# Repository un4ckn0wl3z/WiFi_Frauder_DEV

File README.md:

# WiFi Frauder 🚨📡

**WiFi Frauder** is an open-source hardware and firmware project designed to broadcast humorous or custom WiFi SSIDs using an ESP32-based custom PCB.

---

## 🟩 PCB Overview

---

## 🔧 Features

- Random (Slow) – Randomly spams WiFi SSIDs at a slow rate
- Random (Fast) – Randomly spams WiFi SSIDs at a faster rate
- Custom SSID – Spams WiFi SSIDs based on entries from the SPIFFS config file

---

## To stop spamming
- Press both the UP and DOWN buttons simultaneously to stop spamming.

---

## 🛠️ Hardware

- **Microcontroller**: ESP32 DevKitC 32E (38 pins)
- **Power**: USB or battery-powered
- **Display**: SSD1306 0.96 I2C OLED

PCB design files and schematics are included in the `/pcb` folder.

---

## 📦 Firmware

Written in C++ using the Arduino and FreeRTOS frameworks, built with the PlatformIO toolset.
First, build the SPIFFS file system and edit the SSIDs as you like in the `funny_ssid_list.txt` file located in the `/data` folder.
Then, build the main firmware and upload it to the `WiFi Frauder` device.

---
## Disclaimer

⚠️ Intended for educational and ethical hacking use only. Use responsibly and **never** violate local laws or network policies.

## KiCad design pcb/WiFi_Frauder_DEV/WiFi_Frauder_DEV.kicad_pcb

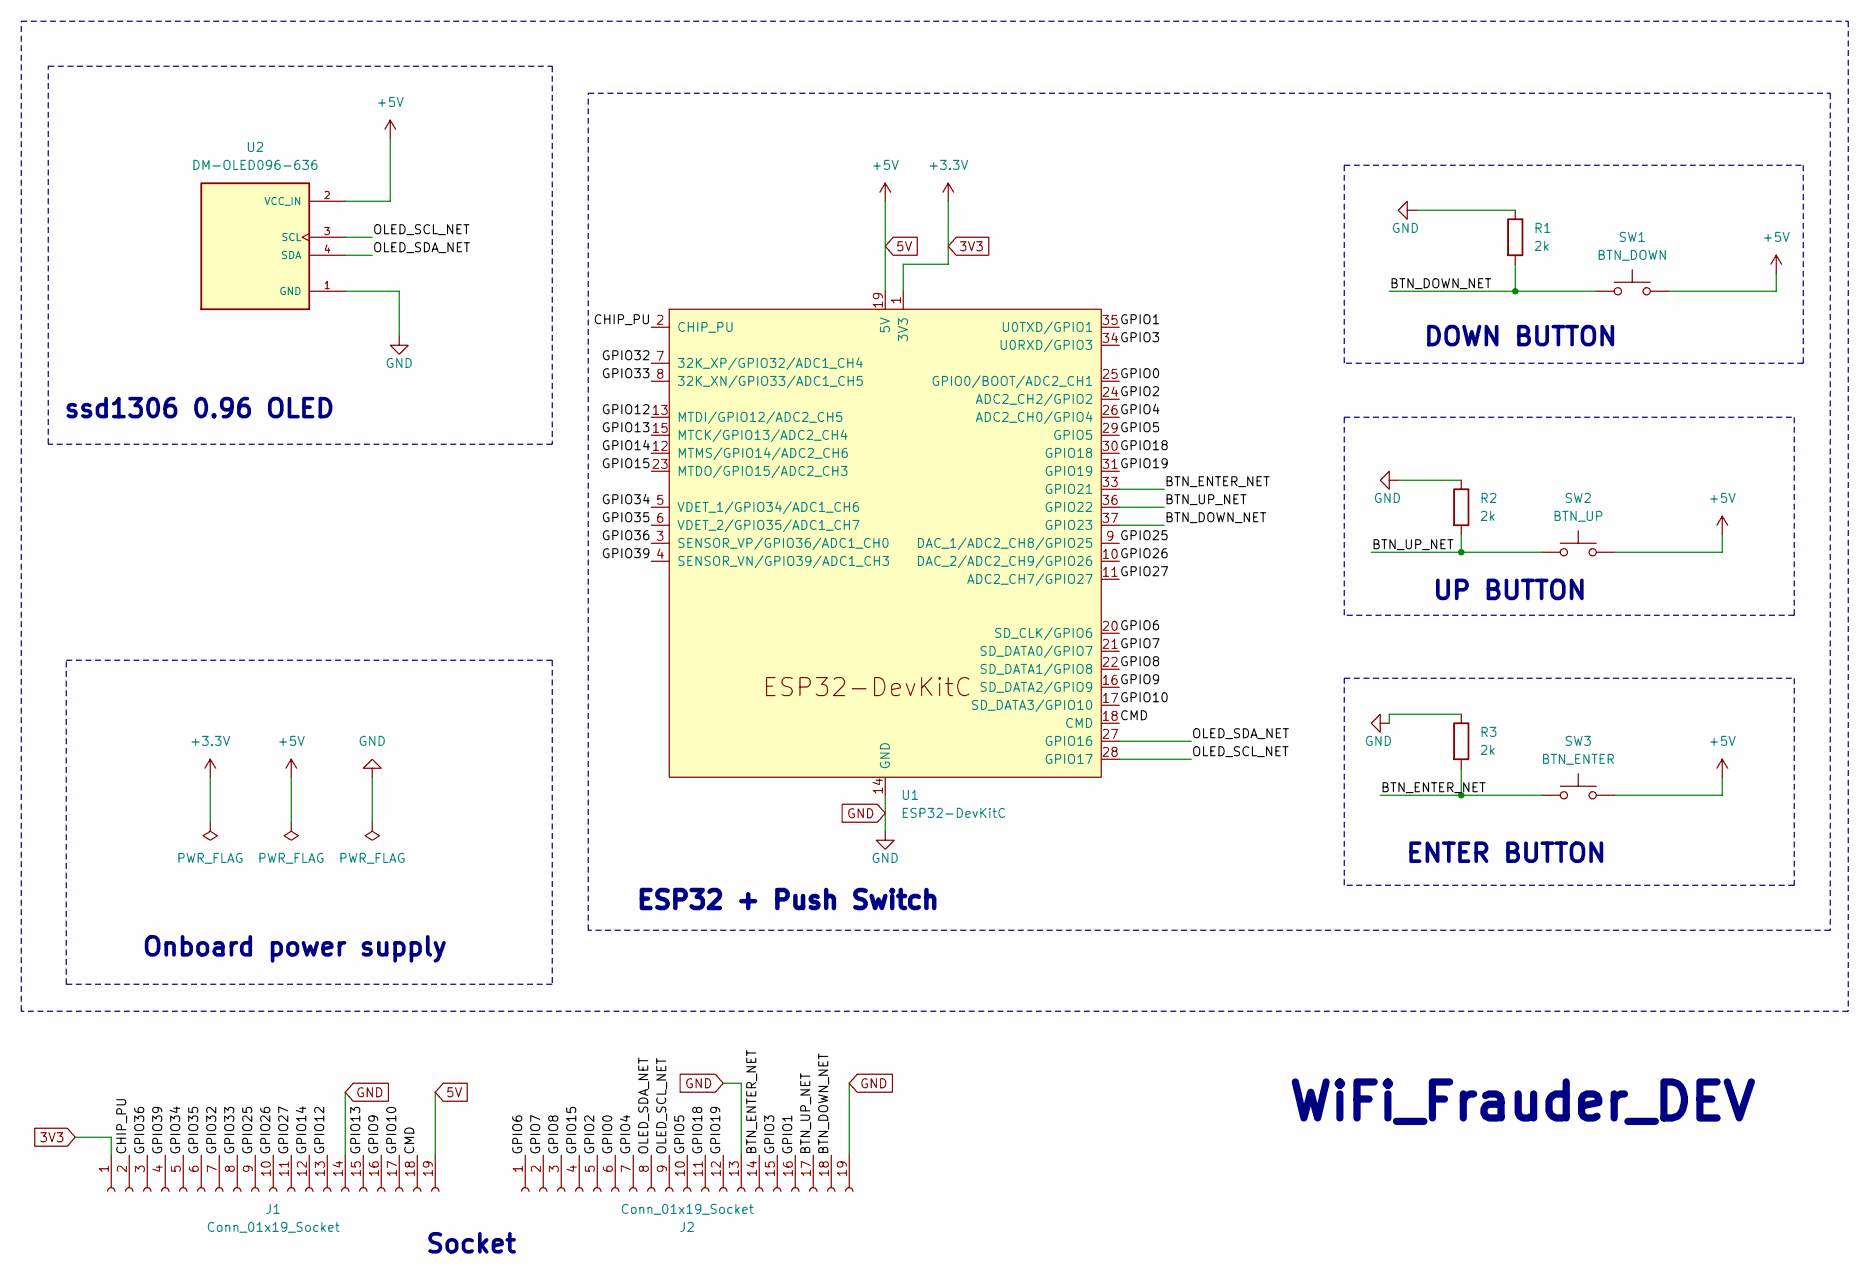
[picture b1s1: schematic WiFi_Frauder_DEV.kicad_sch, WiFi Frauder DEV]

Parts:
J1, J2: Conn_01x19_Socket; PinSocket_1x19_P2.54mm_Vertical
R1, R2, R3: 2k; R_Axial_DIN0207_L6.3mm_D2.5mm_P10.16mm_Horizontal
SW1: BTN_DOWN; SW_PUSH_6mm
SW2: BTN_UP; SW_PUSH_6mm
SW3: BTN_ENTER; SW_PUSH_6mm
U1: ESP32-DevKitC
U2: DM-OLED096-636; MODULE_DM-OLED096-636; PARTREV 2018-09-10

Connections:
3V3: J1.1, U1.1 (3V3)
5V: J1.19, SW1.2, SW2.2, SW3.2, U1.19 (5V), U2.2 (VCC_IN)
/BTN_DOWN_NET: J2.18, R1.2, SW1.1, U1.37 (GPIO23)
/BTN_ENTER_NET: J2.14, R3.2, SW3.1, U1.33 (GPIO21)
/BTN_UP_NET: J2.17, R2.2, SW2.1, U1.36 (GPIO22)
/CHIP_PU: J1.2, U1.2 (CHIP_PU)
/CMD: J1.18, U1.18 (CMD)
/GPIO0: J2.6, U1.25 (GPIO0/BOOT/ADC2_CH1)
/GPIO1: J2.16, U1.35 (U0TXD/GPIO1)
/GPIO2: J2.5, U1.24 (ADC2_CH2/GPIO2)
/GPIO3: J2.15, U1.34 (U0RXD/GPIO3)
/GPIO4: J2.7, U1.26 (ADC2_CH0/GPIO4)
/GPIO5: J2.10, U1.29 (GPIO5)
/GPIO6: J2.1, U1.20 (SD_CLK/GPIO6)
/GPIO7: J2.2, U1.21 (SD_DATA0/GPIO7)
/GPIO8: J2.3, U1.22 (SD_DATA1/GPIO8)
/GPIO9: J1.16, U1.16 (SD_DATA2/GPIO9)
/GPIO10: J1.17, U1.17 (SD_DATA3/GPIO10)
/GPIO12: J1.13, U1.13 (MTDI/GPIO12/ADC2_CH5)
/GPIO13: J1.15, U1.15 (MTCK/GPIO13/ADC2_CH4)
/GPIO14: J1.12, U1.12 (MTMS/GPIO14/ADC2_CH6)
/GPIO15: J2.4, U1.23 (MTDO/GPIO15/ADC2_CH3)
/GPIO18: J2.11, U1.30 (GPIO18)
/GPIO19: J2.12, U1.31 (GPIO19)
/GPIO25: J1.9, U1.9 (DAC_1/ADC2_CH8/GPIO25)
/GPIO26: J1.10, U1.10 (DAC_2/ADC2_CH9/GPIO26)
/GPIO27: J1.11, U1.11 (ADC2_CH7/GPIO27)
/GPIO32: J1.7, U1.7 (32K_XP/GPIO32/ADC1_CH4)
/GPIO33: J1.8, U1.8 (32K_XN/GPIO33/ADC1_CH5)
/GPIO34: J1.5, U1.5 (VDET_1/GPIO34/ADC1_CH6)
/GPIO35: J1.6, U1.6 (VDET_2/GPIO35/ADC1_CH7)
/GPIO36: J1.3, U1.3 (SENSOR_VP/GPIO36/ADC1_CH0)
/GPIO39: J1.4, U1.4 (SENSOR_VN/GPIO39/ADC1_CH3)
/OLED_SCL_NET: J2.9, U1.28 (GPIO17), U2.3 (SCL)
/OLED_SDA_NET: J2.8, U1.27 (GPIO16), U2.4 (SDA)
GND: J1.14, J2.13, J2.19, R1.1, R2.1, R3.1, U1.14 (GND), U1.32 (GND), U1.38 (GND), U2.1 (GND)

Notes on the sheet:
WiFi_Frauder_DEV
ESP32 + Push Switch
Onboard power supply
DOWN BUTTON
ENTER BUTTON
ssd1306 0.96 OLED
UP BUTTON
Socket

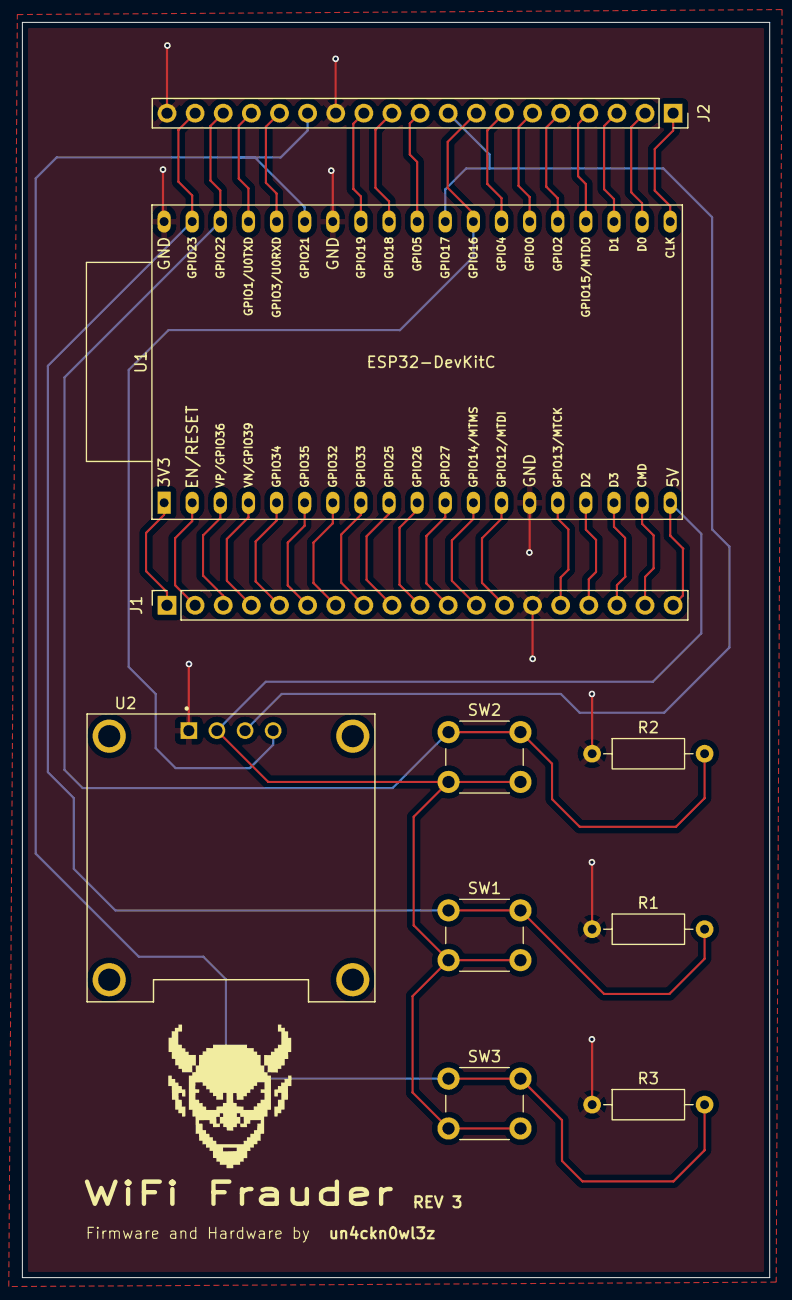
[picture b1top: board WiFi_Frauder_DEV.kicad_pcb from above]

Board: 2 copper layers, 67.5 x 113.4 mm, 10 parts (0 on the bottom side), 36 nets.

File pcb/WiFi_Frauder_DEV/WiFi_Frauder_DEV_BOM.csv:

"Id";"Designator";"Footprint";"Quantity";"Designation";"Supplier and ref";
1;"R2,R1,R3";"C_0805_2012Metric";3;"2k";;;
2;"U2";"MODULE_DM-OLED096-636";1;"DM-OLED096-636";;;
3;"SW2";"SW_PUSH_6mm";1;"BTN_UP";;;
4;"SW3";"SW_PUSH_6mm";1;"BTN_ENTER";;;
5;"U1";"ESP32-DevKitC";1;"ESP32-DevKitC";;;
6;"SW1";"SW_PUSH_6mm";1;"BTN_DOWN";;;

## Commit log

2025-06-08 chore: refactoring codebase
2025-06-08 fix: typo
2025-06-08 fix: ssid list name
2025-06-08 feat: add pcb
2025-06-08 feat: screenshot
2025-06-10 feat: revision PCB from 0 to 1
2025-06-10 fix: schema typo
2025-06-11 feat: update README
2025-06-12 feat: revistion pcb to rev2
2025-06-12 feat: update screenshot
2025-06-13 feat: hardware monkey patch pinout
2025-06-14 fix: correct schema pinout; remove strapping pin
2025-06-14 feat: re-design pcb
2025-06-18 feat: re-designed pcb included extended female socket for GPIO
2025-06-24 feat: add pcb assemble example
2025-06-24 feat: update menu style
2025-06-24 feat: update
2025-06-24 fix: display task bug
2025-06-24 fix: minor
2025-06-24 fea: play with cc1101 jammer
